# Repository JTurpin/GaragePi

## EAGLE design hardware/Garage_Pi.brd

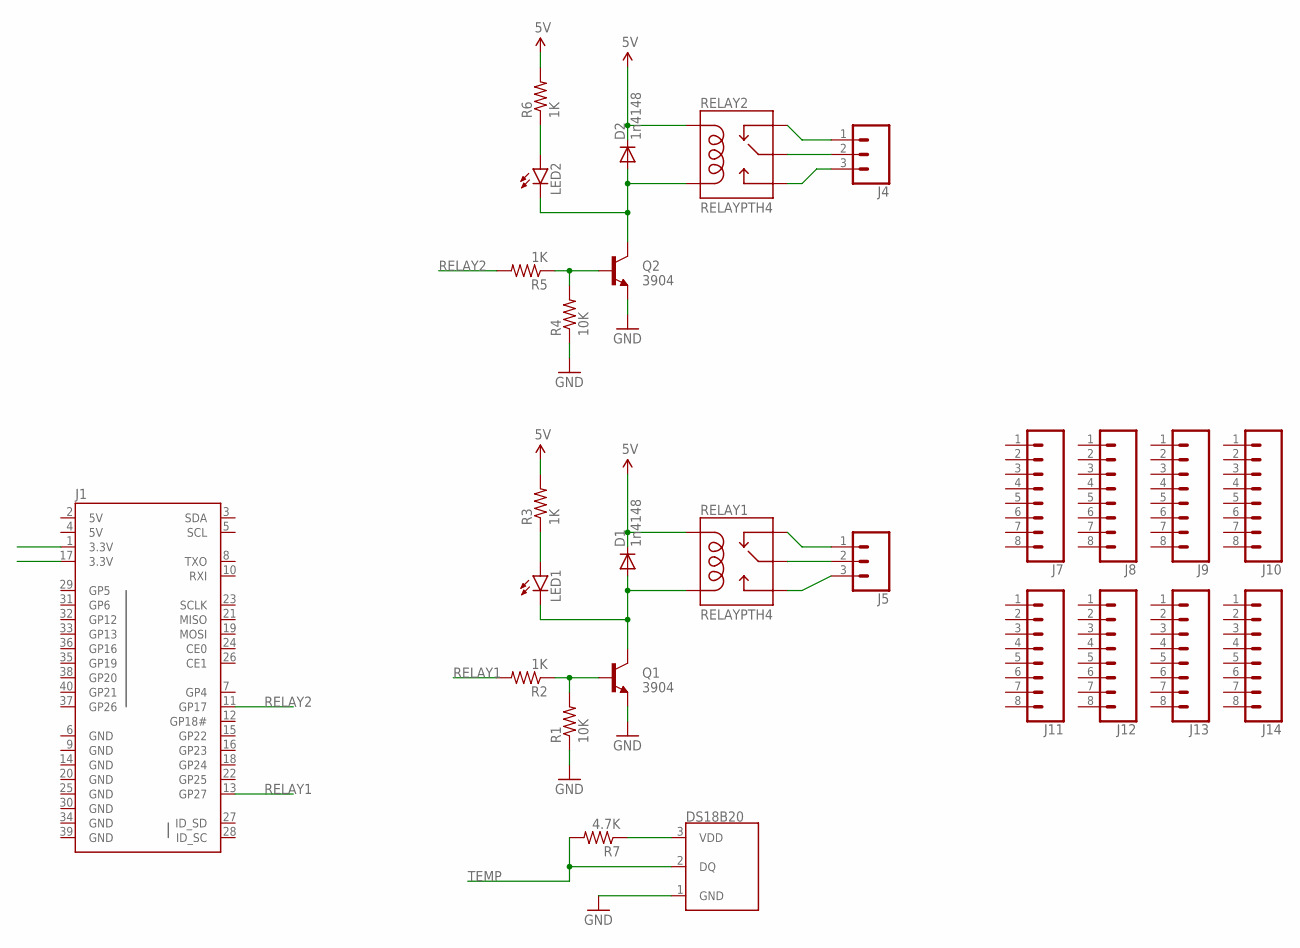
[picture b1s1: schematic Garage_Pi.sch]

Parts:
D1, D2: 1n4148; SOD-123_MINI-SMA
DS18B20: DS18B20; TO-92-AMMO
J1: RASPBERRYPI-40-PIN-GPIO_PTH; 2X20_SHROUDED
J4, J5: CONN_03SCREW; SCREWTERMINAL-3.5MM-3
J7, J8, J9, J10, J11, J12, J13, J14: CONN_08NO_SILK_FEMALE_PTH; 1X08_NO_SILK
LED1, LED2: LED-FKIT-1206; FKIT-LED-1206
Q1, Q2: 3904; SOT23-3
R1, R4: 10K; 0805
R2, R3, R5, R6: 1K; 0805
R7: 4.7K; 0805
RELAY1, RELAY2: RELAYPTH4; RELAY-JZC

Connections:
3.3V: DS18B20.3 (VDD), J1.1 (3.3V), R7.1
5V: D1.C, D2.C, J1.2 (5V), J1.4 (5V), R3.2, R6.2, RELAY1.5 (COIL1), RELAY2.5 (COIL1)
COM1: J5.2, RELAY1.4 (MAIN)
COM2: J4.2, RELAY2.4 (MAIN)
GND: DS18B20.1 (GND), J1.6 (GND), J1.9 (GND), J1.14 (GND), J1.20 (GND), J1.25 (GND), J1.30 (GND), J1.34 (GND), J1.39 (GND), Q1.2 (E), Q2.2 (E), R1.1, R4.1
unnamed: Q1.1 (B), R1.2, R2.1
unnamed: D1.A, LED1.C, Q1.3 (C), RELAY1.1 (COIL2)
unnamed: LED1.A, R3.1
unnamed: D2.A, LED2.C, Q2.3 (C), RELAY2.1 (COIL2)
unnamed: Q2.1 (B), R4.2, R5.1
unnamed: LED2.A, R6.1
NC1: J5.1, RELAY1.2 (NC)
NC2: J4.1, RELAY2.2 (NC)
NO1: J5.3, RELAY1.3 (NO)
NO2: J4.3, RELAY2.3 (NO)
RELAY1: J1.13 (GP27), R2.2
RELAY2: J1.11 (GP17), R5.2
TEMP: DS18B20.2 (DQ), R7.2

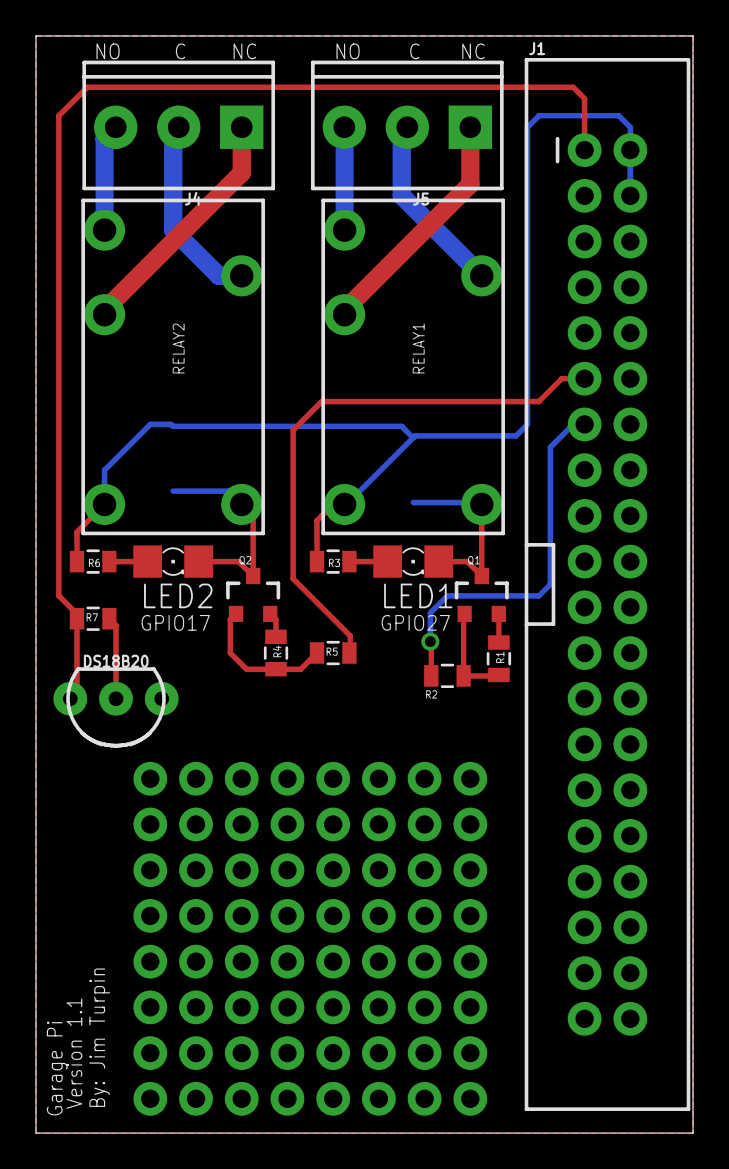
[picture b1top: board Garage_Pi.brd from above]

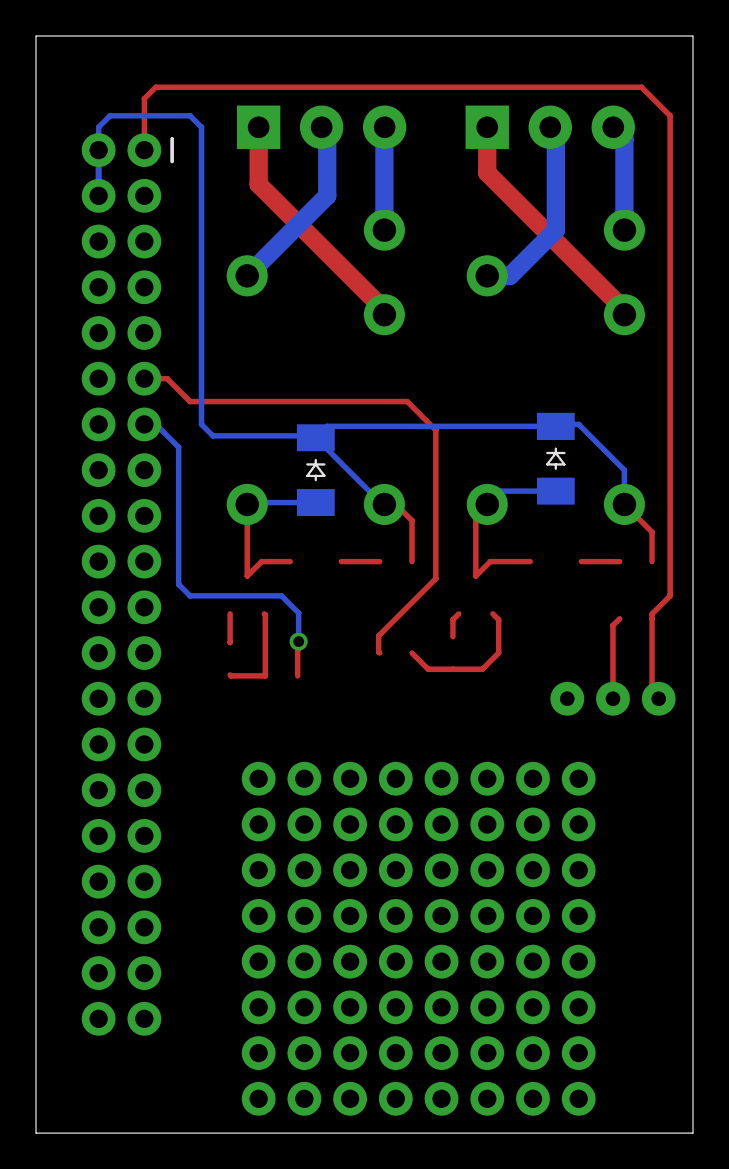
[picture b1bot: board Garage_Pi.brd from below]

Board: 2 copper layers, 36.5 x 61.0 mm, 27 parts (2 on the bottom side), 18 nets.

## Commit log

2017-02-24 adding hardware

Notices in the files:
parts and their libraries:
SparkFun-Connectors: Licensing: Creative Commons ShareAlike 4.0 International - https://creativecommons.org/licenses/by-sa/4.0
